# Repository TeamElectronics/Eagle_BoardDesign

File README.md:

# Eagle_BoardDesign
Repository containing all files for the pub board design on Eagle

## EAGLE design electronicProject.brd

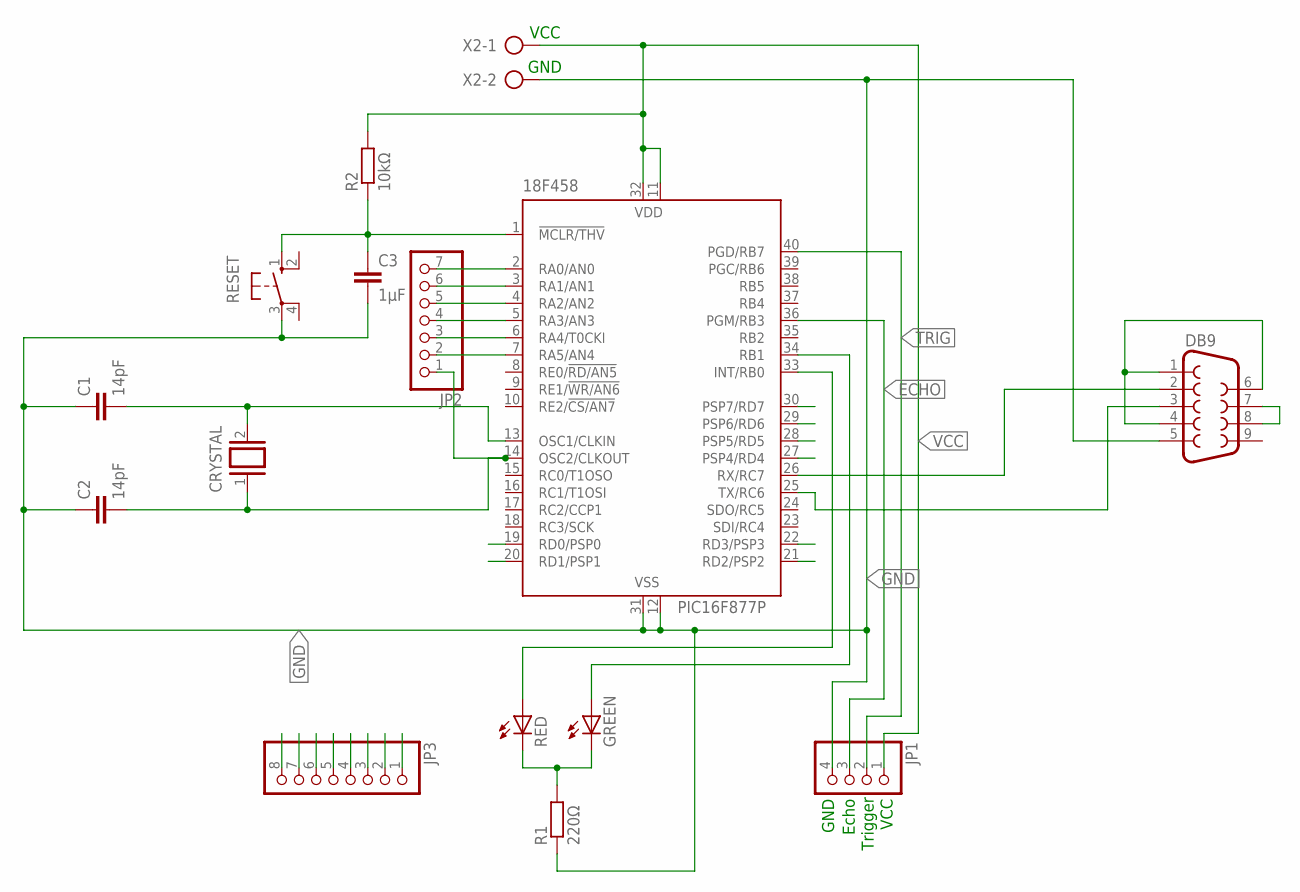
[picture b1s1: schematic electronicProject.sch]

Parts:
18F458: PIC16F877P; DIL40
C1, C2: 14pF; C025-024X044
C3: 1µF; C025-024X044
CRYSTAL: XTAL/S; QS
DB9: F09H
GREEN: LED3MM
JP1: PINHD-1X4; 1X04
JP2: PINHD-1X7; 1X07
JP3: PINHD-1X8; 1X08
R1: 220Ω; 0207/10
R2: 10kΩ; 0207/10
RED: LED3MM
RESET: 10-XX; B3F-10XX
X2: AK300/2

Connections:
ECHO: 18F458.36 (PGM/RB3), JP1.3
GND: 18F458.12 (VSS), 18F458.31 (VSS), C1.1, C2.1, C3.2, DB9.5, JP1.4, R1.1, RESET.3, X2.2
unnamed: 18F458.34 (RB1), GREEN.A
unnamed: 18F458.33 (INT/RB0), RED.A
unnamed: 18F458.1 (!MCLR/THV), C3.1, R2.1, RESET.1 (S)
unnamed: 18F458.2 (RA0/AN0), JP2.7
unnamed: 18F458.3 (RA1/AN1), JP2.6
unnamed: 18F458.4 (RA2/AN2), JP2.5
unnamed: DB9.1, DB9.4, DB9.6
unnamed: 18F458.26 (RX/RC7), DB9.2
unnamed: DB9.7, DB9.8
unnamed: 18F458.5 (RA3/AN3), JP2.4
unnamed: 18F458.25 (TX/RC6), DB9.3
unnamed: 18F458.6 (RA4/T0CKI), JP2.3
unnamed: 18F458.7 (RA5/AN4), JP2.2
unnamed: 18F458.13 (OSC1/CLKIN), C1.2, CRYSTAL.2
unnamed: 18F458.14 (OSC2/CLKOUT), C2.2, CRYSTAL.1, JP2.1
unnamed: GREEN.K (C), R1.2, RED.K (C)
RD0: 18F458.19 (RD0/PSP0), JP3.8
RD1: 18F458.20 (RD1/PSP1), JP3.7
RD2: 18F458.21 (RD2/PSP2), JP3.6
RD3: 18F458.22 (RD3/PSP3), JP3.5
RD4: 18F458.27 (PSP4/RD4), JP3.4
RD5: 18F458.28 (PSP5/RD5), JP3.3
RD6: 18F458.29 (PSP6/RD6), JP3.2
RD7: 18F458.30 (PSP7/RD7), JP3.1
TRIG: 18F458.40 (PGD/RB7), JP1.2
VCC: 18F458.11 (VDD), 18F458.32 (VDD), JP1.1, R2.2, X2.1

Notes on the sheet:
VCC
GND
Trigger
Echo

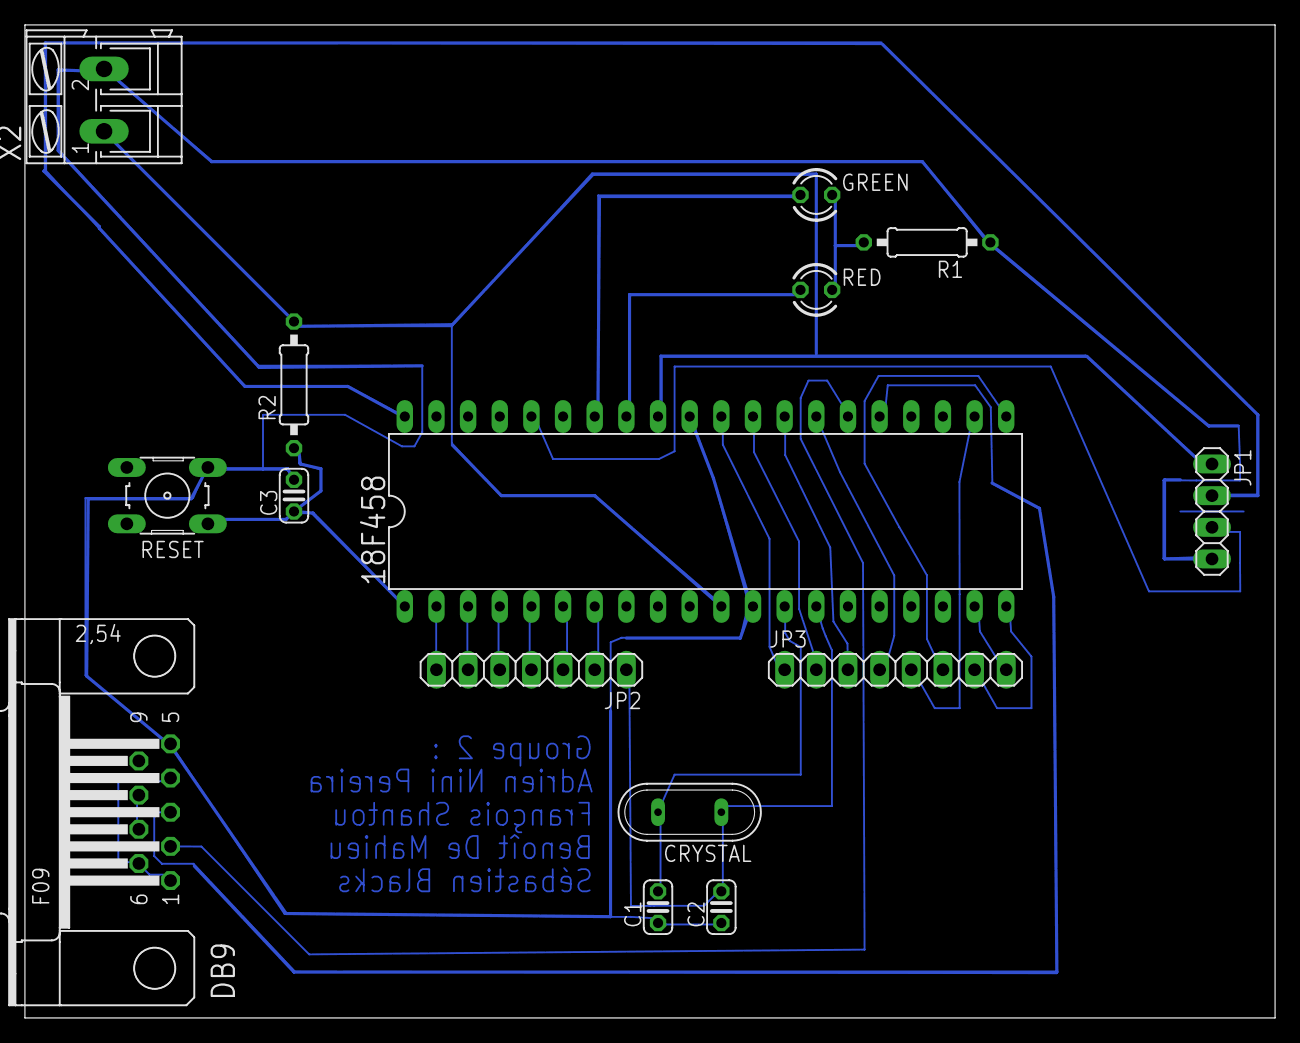
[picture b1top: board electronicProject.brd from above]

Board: 2 copper layers, 100.3 x 79.7 mm, 15 parts (0 on the bottom side), 28 nets.

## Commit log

2018-02-25 Board Logic Design
2018-02-26 UPDATE Datasheets
2018-02-26 Routing
2018-02-26 Update PCB design
    Add Group and names on PCB
2018-02-27 Board UPDATE
    Correction sonde à ultrasons (rotation 180°)
    Reroutage des pattes de la sonde
2018-03-16 final design
2018-03-16 Finale file
